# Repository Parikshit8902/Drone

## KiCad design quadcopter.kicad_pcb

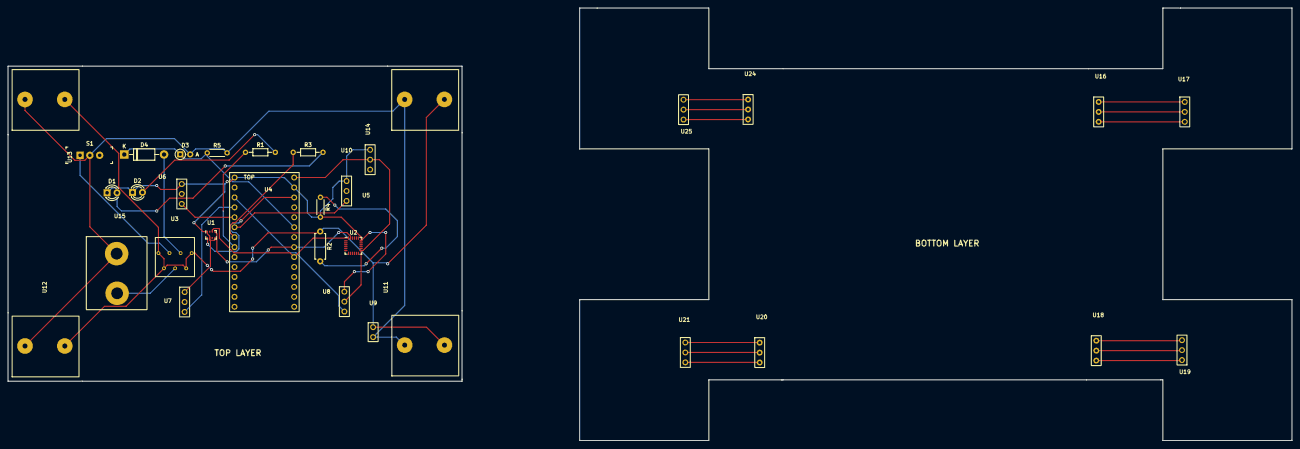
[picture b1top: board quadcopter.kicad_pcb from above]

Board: 2 copper layers, 328.1 x 110.5 mm, 33 parts (0 on the bottom side), 32 nets.

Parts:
D1: RED; LED_D3.0mm
D2: GREEN; LED_D3.0mm
D3: D_Zener; D_DO-35_SOD27_P2.54mm_Vertical_AnodeUp
D4: 1N4007; D_DO-41_SOD81_P10.16mm_Horizontal
R1, R3: 100 ohm; R_Axial_DIN0204_L3.6mm_D1.6mm_P7.62mm_Horizontal
R2: 2k ohm; R_Axial_DIN0207_L6.3mm_D2.5mm_P7.62mm_Horizontal
R4, R5: 510 ohm; R_Axial_DIN0204_L3.6mm_D1.6mm_P5.08mm_Horizontal
S1: EG1218; Switch_Slide_11.6x4mm_EG1218
U1: BMP280; Bosch_LGA-8_2x2.5mm_P0.65mm_ClockwisePinNumbering
U2: MPU-6050; InvenSense_QFN-24_4x4mm_P0.5mm
U3: bts_symbol
U4: Teensy4.0; teensy4.0uc
U5: Motor_4; motor_U
U6: Motor_3; motor_U
U7: Motor_2; motor_U
U8: Motor_1; motor_U
U9: External Power; External_Power
U10: Receiver
U11: ESC_1; ESC
U12: ESC_2; ESC
U13: ESC_3; ESC
U14: ESC_4; ESC
U15: Battery; battery
U16: ESC_3 hole1; esc_3pin
U17: Motor_3 hole1; motor
U18: ESC_3 hole2; esc_3pin
U19: Motor_3 hole2; motor
U20: ESC_3 hole4; esc_3pin
U21: Motor_3 hole4; motor
U24: ESC_3 hole3; esc_3pin
U25: Motor_3 hole3; motor

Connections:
0HV: D3.2 (A), R5.2, S1.2, U9.1 (G), U11.1 (0), U12.1 (0), U13.1 (0), U14.1 (0), U15.1 (0V)
3V: U1.8 (VDD), U4.26 (3V)
5V: U2.13 (VDD), U4.28 (5V), U8.2 (VCC), U10.2 (VCC)
76HV: R2.1, U3.1 (OUT), U3.2 (OUT), U3.6 (OUT), U3.7 (OUT), U9.2 (7.6V), U11.2 (7.4), U12.2 (7.4), U13.2 (7.4), U14.2 (7.4)
BTS_IS: D4.2 (A), U3.5 (IS)
GND: D1.1 (K), D2.1 (K), R4.2, U1.1 (GND), U1.5 (SDO), U1.7 (GND), U2.18 (GND), U4.1 (G), U4.27 (G), U5.1 (GND), U6.1 (GND), U7.1 (GND), U8.1 (GND), U10.1 (GND)
GREENLED: R1.1, U4.8 (6)
Motor1: U4.3 (1), U8.3 (SIG)
Motor2: U4.4 (2), U7.3 (SIG)
Motor3: U4.5 (3), U6.3 (SIG)
Motor4: U4.6 (4), U5.3 (SIG)
unnamed: D1.2 (A), R3.2
unnamed: D2.2 (A), R1.2
unnamed: U3.4 (Vbb), U15.2 (7.4V)
unnamed: U16.3 (BLACK), U17.3 (LOWER)
unnamed: U16.2 (BLUE), U17.2 (MIDDLE)
unnamed: U16.1 (RED), U17.1 (UPPER)
unnamed: U18.3 (BLACK), U19.1 (UPPER)
unnamed: U18.2 (BLUE), U19.2 (MIDDLE)
unnamed: U18.1 (RED), U19.3 (LOWER)
unnamed: U20.3 (BLACK), U21.3 (LOWER)
unnamed: U20.2 (BLUE), U21.2 (MIDDLE)
unnamed: U20.1 (RED), U21.1 (UPPER)
unnamed: U24.3 (BLACK), U25.1 (UPPER)
unnamed: U24.2 (BLUE), U25.2 (MIDDLE)
unnamed: U24.1 (RED), U25.3 (LOWER)
REDLED: R3.1, U4.7 (5)
RESISTOR: R2.2, R4.1
SCL: U1.4 (SCK), U2.23 (SCL), U4.21 (19)
SDA: U1.3 (SDI), U2.24 (SDA), U4.20 (18)
SWITCH: S1.1, U3.3 (IN)
V_IS: D3.1 (K), D4.1 (K), R5.1, U4.23 (21)
